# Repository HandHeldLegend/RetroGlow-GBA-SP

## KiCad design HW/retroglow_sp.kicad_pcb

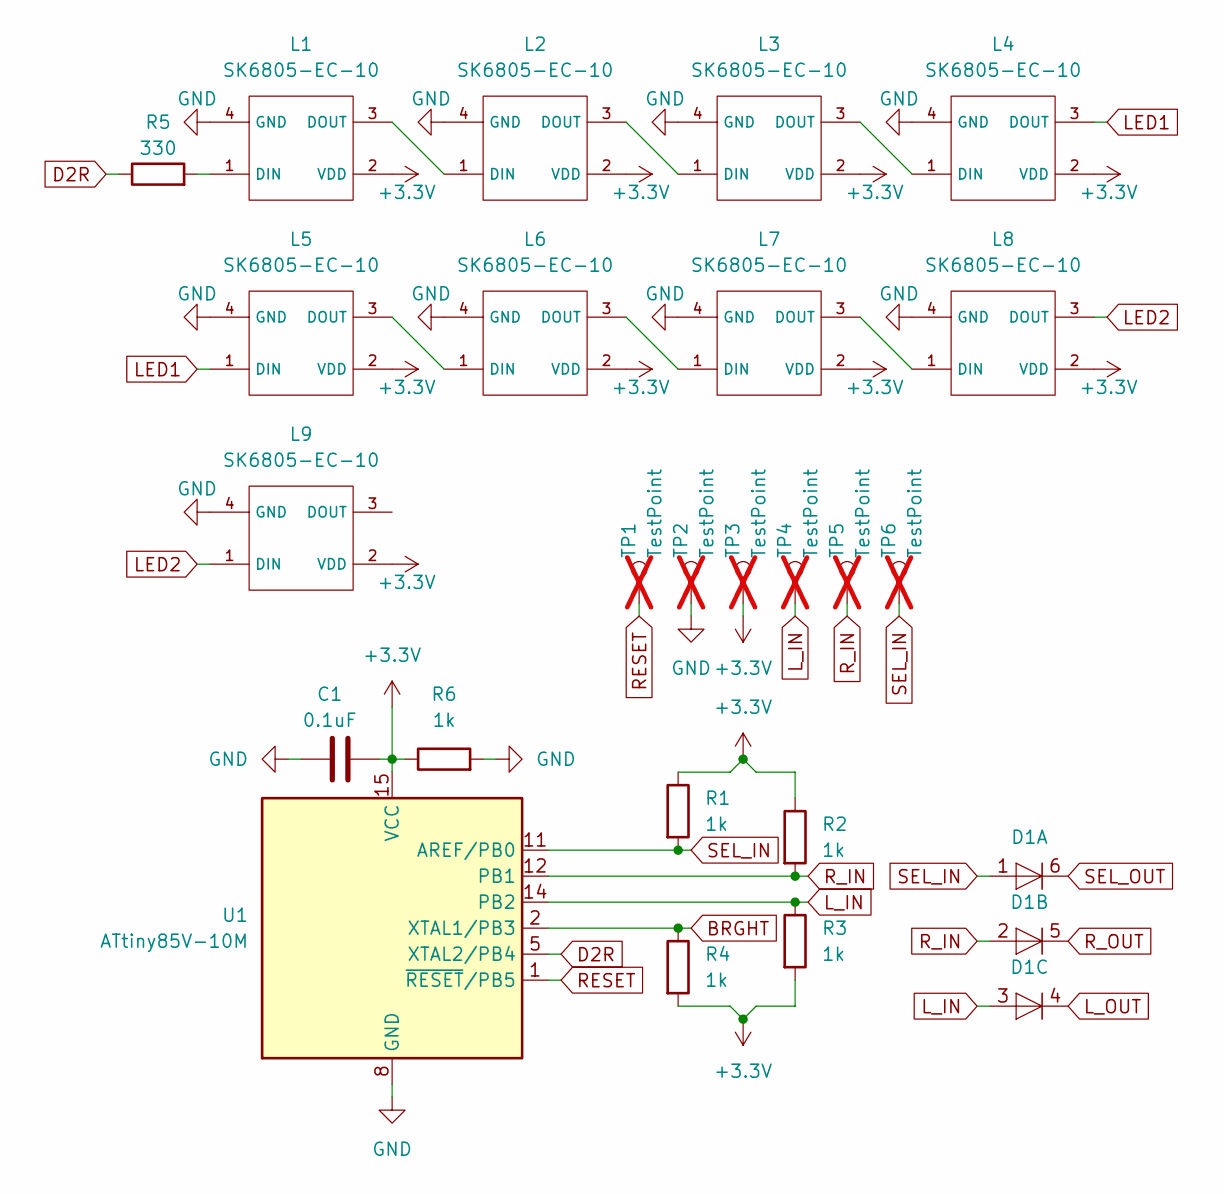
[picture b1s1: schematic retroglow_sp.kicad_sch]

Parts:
C1: 0.1uF; C_0805_2012Metric; MPN C0805B104K500NT
D1: BAS16VY,115; SOT-363_SC-70-6; MPN BAS16VY,115
L1, L2, L3, L4, L5, L6, L7, L8, L9: SK6805-EC-10; MPN SK6805-EC-10
R1, R2, R3, R4, R6: 1k; R_0402_1005Metric; MPN 0402WGF1001TCE
R5: 330; R_0402_1005Metric; MPN 0402WGF3300TCE
TP1, TP2, TP3, TP4, TP5, TP6: TestPoint; TestPoint_Pad_D1.0mm; not fitted
U1: ATtiny85V-10M; QFN-20-1EP_4x4mm_P0.5mm_EP2.6x2.6mm; MPN ATtiny85V-10M

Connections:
+3.3V: C1.2, L1.2 (VDD), L2.2 (VDD), L3.2 (VDD), L4.2 (VDD), L5.2 (VDD), L6.2 (VDD), L7.2 (VDD), L8.2 (VDD), L9.2 (VDD), R1.1, R2.1, R3.2, R4.2, R6.1, TP3.1, U1.15 (VCC)
BRGHT: R4.1, U1.2 (XTAL1/PB3)
D2R: R5.1, U1.5 (XTAL2/PB4)
GND: C1.1, L1.4 (GND), L2.4 (GND), L3.4 (GND), L4.4 (GND), L5.4 (GND), L6.4 (GND), L7.4 (GND), L8.4 (GND), L9.4 (GND), R6.2, TP2.1, U1.8 (GND), U1.21 (GND)
LED1: L4.3 (DOUT), L5.1 (DIN)
LED2: L8.3 (DOUT), L9.1 (DIN)
L_IN: D1.3 (A), R3.1, TP4.1, U1.14 (PB2)
L_OUT: D1.4 (K)
unnamed: L1.1 (DIN), R5.2
unnamed: L1.3 (DOUT), L2.1 (DIN)
unnamed: L2.3 (DOUT), L3.1 (DIN)
unnamed: L3.3 (DOUT), L4.1 (DIN)
unnamed: L5.3 (DOUT), L6.1 (DIN)
unnamed: L6.3 (DOUT), L7.1 (DIN)
unnamed: L7.3 (DOUT), L8.1 (DIN)
RESET: TP1.1, U1.1 (~RESET/PB5)
R_IN: D1.2 (A), R2.2, TP5.1, U1.12 (PB1)
R_OUT: D1.5 (K)
SEL_IN: D1.1 (A), R1.2, TP6.1, U1.11 (AREF/PB0)
SEL_OUT: D1.6 (K)

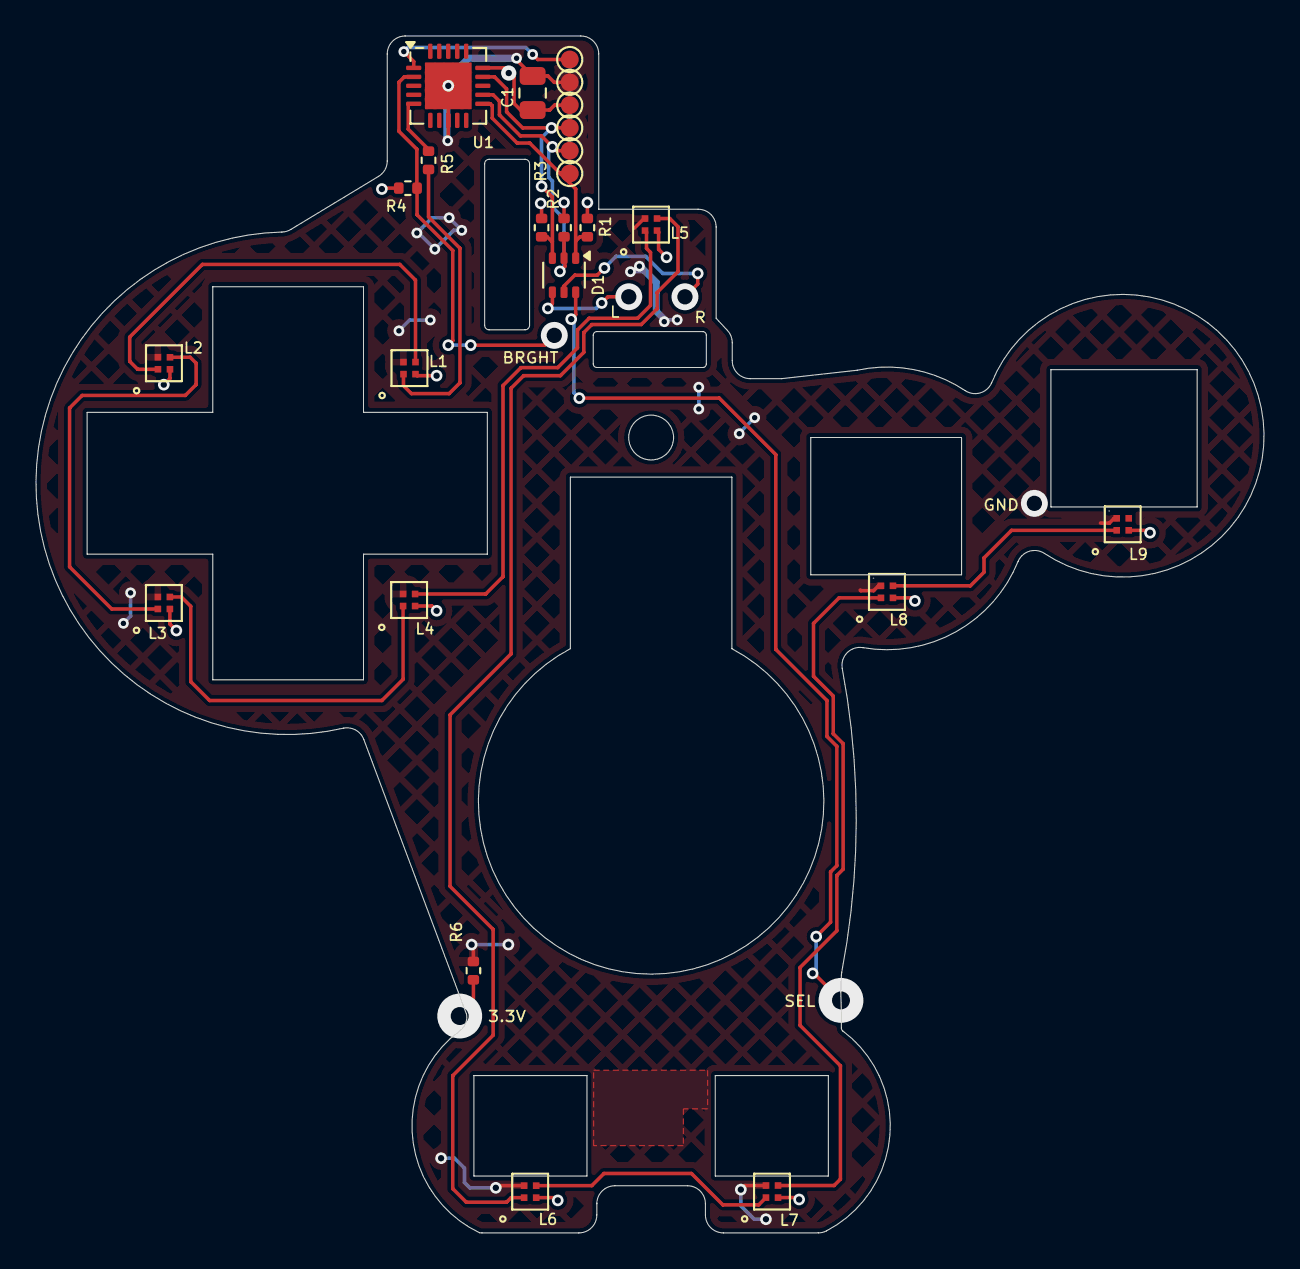
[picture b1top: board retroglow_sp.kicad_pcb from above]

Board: 2 copper layers, 68.4 x 66.7 mm, 24 parts (0 on the bottom side), 17 nets.

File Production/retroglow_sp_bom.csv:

"Reference","MPN","Value","Datasheet","Footprint","Qty","DNP"
"C1","C0805B104K500NT","0.1uF","~","Capacitor_SMD:C_0805_2012Metric","1",""
"D1","BAS16VY,115","BAS16VY,115","","Package_TO_SOT_SMD:SOT-363_SC-70-6","1",""
"L1,L2,L3,L4,L5,L6,L7,L8,L9","SK6805-EC-10","SK6805-EC-10","https://cdn-shop.adafruit.com/product-files/5849/SK6805-EC10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","hhl:SK6805-EC-10","9",""
"R1,R2,R3,R4,R6","0402WGF1001TCE","1k","~","Resistor_SMD:R_0402_1005Metric","5",""
"R5","0402WGF3300TCE","330","~","Resistor_SMD:R_0402_1005Metric","1",""
"TP1,TP2,TP3,TP4,TP5,TP6","","TestPoint","~","TestPoint:TestPoint_Pad_D1.0mm","6","DNP"
"U1","ATtiny85V-10M","ATtiny85V-10M","http://ww1.microchip.com/downloads/en/DeviceDoc/atmel-2586-a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","Package_DFN_QFN:QFN-20-1EP_4x4mm_P0.5mm_EP2.6x2.6mm","1",""

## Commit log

2022-04-19 Added brightness control option
    Allows for brightness control when using housings that do not have a brightness button.
2022-04-21 Fixed saving bug
    - Added auto-save brightness whenever that option is changed
    - Fixed bug where colors would not save in some circumstances.
2024-11-22 Updates to PCB
